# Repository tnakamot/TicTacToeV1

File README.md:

# Tic-Tac-Toe V1

This is a project to make a Tic-Tac-Toe game using Arduino Nano.

## PCB

 * The PCB has been designed with [KiCAD 6.0.10](https://www.kicad.org/).
 * The KiCAD project is available in [KiCAD/](KiCAD/) directory.

<p float="left">

</p>

The pictures below show the PCB manufactured by [OSHPARK](https://oshpark.com/).

## Software

(TODO: explain how to install the software on the Arduino Nano.)

## Parts

The list below shows the parts that this project uses.

 * Arduino Nano
   * [Product webpage at Arduino.cc](https://docs.arduino.cc/hardware/nano)
   * [Datasheet](https://docs.arduino.cc/static/2d169cbfd360faf817882e36b9f69956/A000005-datasheet.pdf)
   * This project uses a compatible clone (Arduino Nano CH340).
 * Omron B3W-9000-RG2C: button with two LEDs (red and green)
   * [Product webpage at Omron](https://components.omron.com/eu-en/products/switches/B3W-9)
   * [Datasheet](https://components.omron.com/eu-en/datasheet_pdf/A167-E1.pdf)
   * [Product page at Mouser](https://www.mouser.com/ProductDetail/Omron-Electronics/B3W-9000-RG2C?qs=QTkYtwcxD6NNQk1oSF8osQ%3D%3D): includes the link to footprint.
   * [3D Model at SnapEDA](https://www.snapeda.com/parts/B3W-9000-RG2C/Omron%20Electronics/view-part/?ref=digikey)
 * Texas Instruments 74HC165: 8-bit parallel-load shift register
   * [Product webpage at Texas Instruments](https://www.ti.com/product/SN74HC165)
   * [Datasheet](https://www.ti.com/lit/ds/symlink/sn74hc165.pdf)
 * Analog Devices MAX7219: serially interfaced, LED display driver
   * [Product webpage at Analog Devices](https://www.analog.com/en/products/max7219.html)
   * [Datasheet](https://www.analog.com/media/en/technical-documentation/data-sheets/MAX7219-MAX7221.pdf)
   * [LedControl - An Arduino library for the MAX7219 and MAX7221](http://wayoda.github.io/LedControl/index.html)
     * This program uses this library to control MAX7219.
     * The page above also explains how to wire up LEDs to MAX7219.
     
## License

TBD

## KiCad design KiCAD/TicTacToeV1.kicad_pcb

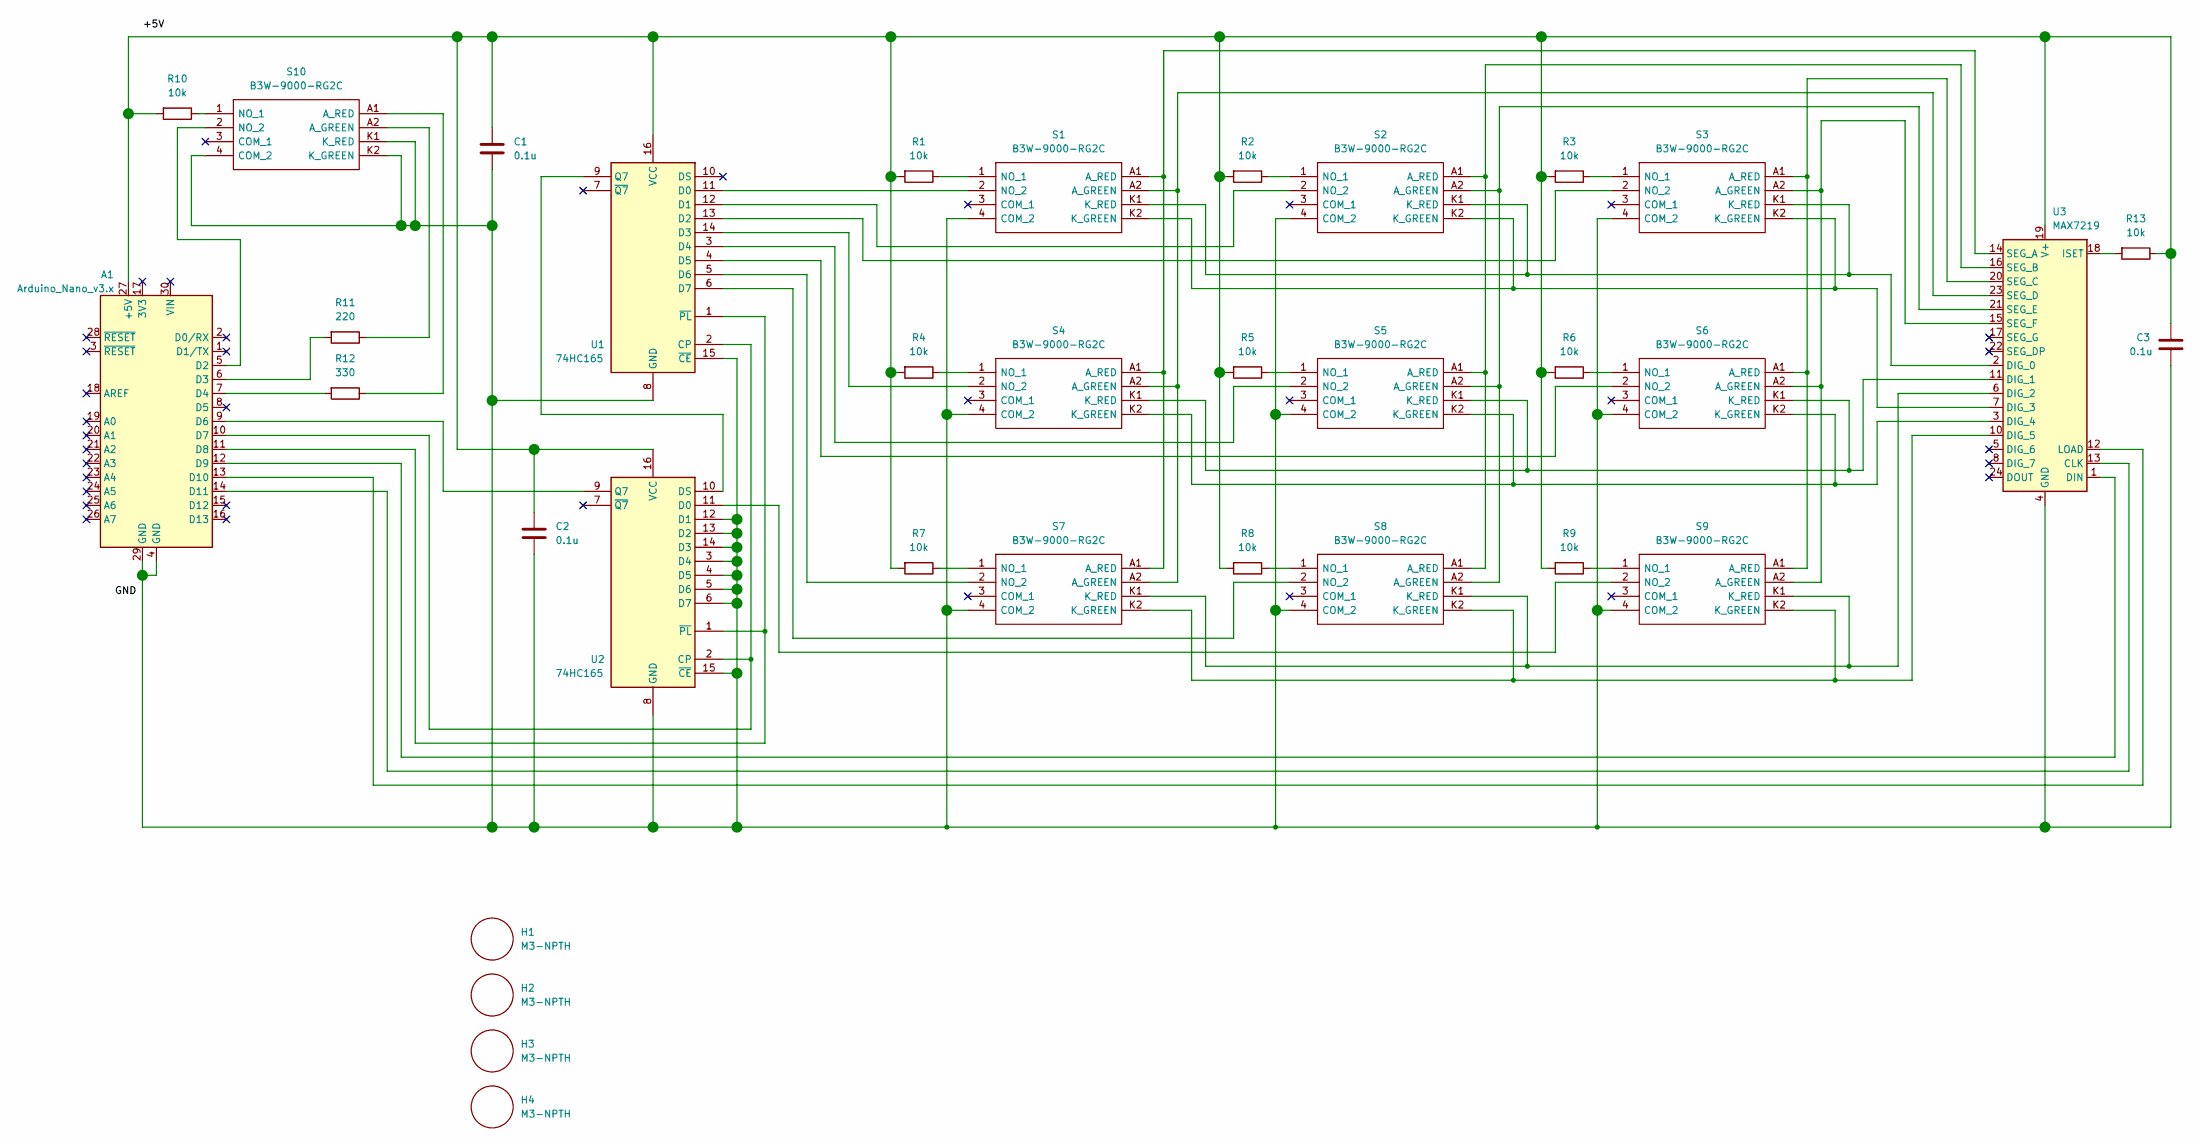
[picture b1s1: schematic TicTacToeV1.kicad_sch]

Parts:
A1: Arduino_Nano_v3.x; Arduino_Nano
C1, C2, C3: 0.1u; C_Disc_D5.0mm_W2.5mm_P5.00mm
H1, H2, H3, H4: M3-NPTH
R1, R2, R3, R4, R5, R6, R7, R8, R9, R10, R13: 10k; R_Axial_DIN0207_L6.3mm_D2.5mm_P15.24mm_Horizontal
R11: 220; R_Axial_DIN0207_L6.3mm_D2.5mm_P15.24mm_Horizontal
R12: 330; R_Axial_DIN0207_L6.3mm_D2.5mm_P15.24mm_Horizontal
S1, S2, S3, S4, S5, S6, S7, S8, S9, S10: B3W-9000-RG2C; Mouser Part Number 653-B3W-9000-RG2C
U1, U2: 74HC165; DIP-16_W7.62mm
U3: MAX7219; DIP-24_W7.62mm

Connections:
unnamed: A1.5 (D2), S10.2 (NO_2)
unnamed: A1.6 (D3), R11.2
unnamed: A1.7 (D4), R12.2
unnamed: A1.9 (D6), U2.9 (Q7)
unnamed: A1.10 (D7), U1.2 (CP), U2.2 (CP)
unnamed: A1.11 (D8), U1.1 (~PL), U2.1 (~PL)
unnamed: A1.12 (D9), U3.1 (DIN)
unnamed: A1.13 (D10), U3.12 (LOAD)
unnamed: A1.14 (D11), U3.13 (CLK)
unnamed: A1.27 (+5V), C1.1, C2.1, C3.1, R1.2, R2.2, R3.2, R4.2, R5.2, R6.2, R7.2, R8.2, R9.2, R10.2, R13.1, U1.16 (VCC), U2.16 (VCC), U3.19 (V+)
unnamed: A1.4 (GND), A1.29 (GND), C1.2, C2.2, C3.2, S1.4 (COM_2), S2.4 (COM_2), S3.4 (COM_2), S4.4 (COM_2), S5.4 (COM_2), S6.4 (COM_2), S7.4 (COM_2), S8.4 (COM_2), S9.4 (COM_2), S10.4 (COM_2), S10.K1 (K_RED), S10.K2 (K_GREEN), U1.8 (GND), U1.15 (~CE), U2.3 (D4), U2.4 (D5), U2.5 (D6), U2.6 (D7), U2.8 (GND), U2.12 (D1), U2.13 (D2), U2.14 (D3), U2.15 (~CE), U3.4 (GND), U3.9 (GND)
unnamed: R1.1, S1.1 (NO_1)
unnamed: R2.1, S2.1 (NO_1)
unnamed: R3.1, S3.1 (NO_1)
unnamed: R4.1, S4.1 (NO_1)
unnamed: R5.1, S5.1 (NO_1)
unnamed: R6.1, S6.1 (NO_1)
unnamed: R7.1, S7.1 (NO_1)
unnamed: R8.1, S8.1 (NO_1)
unnamed: R9.1, S9.1 (NO_1)
unnamed: R10.1, S10.1 (NO_1)
unnamed: R11.1, S10.A2 (A_GREEN)
unnamed: R12.1, S10.A1 (A_RED)
unnamed: R13.2, U3.18 (ISET)
unnamed: S1.2 (NO_2), U1.11 (D0)
unnamed: S1.A1 (A_RED), S4.A1 (A_RED), S7.A1 (A_RED), U3.14 (SEG_A)
unnamed: S1.A2 (A_GREEN), S4.A2 (A_GREEN), S7.A2 (A_GREEN), U3.23 (SEG_D)
unnamed: S1.K1 (K_RED), S2.K1 (K_RED), S3.K1 (K_RED), U3.2 (DIG_0)
unnamed: S1.K2 (K_GREEN), S2.K2 (K_GREEN), S3.K2 (K_GREEN), U3.7 (DIG_3)
unnamed: S2.2 (NO_2), U1.12 (D1)
unnamed: S2.A1 (A_RED), S5.A1 (A_RED), S8.A1 (A_RED), U3.16 (SEG_B)
unnamed: S2.A2 (A_GREEN), S5.A2 (A_GREEN), S8.A2 (A_GREEN), U3.21 (SEG_E)
unnamed: S3.2 (NO_2), U1.13 (D2)
unnamed: S3.A1 (A_RED), S6.A1 (A_RED), S9.A1 (A_RED), U3.20 (SEG_C)
unnamed: S3.A2 (A_GREEN), S6.A2 (A_GREEN), S9.A2 (A_GREEN), U3.15 (SEG_F)
unnamed: S4.2 (NO_2), U1.14 (D3)
unnamed: S4.K1 (K_RED), S5.K1 (K_RED), S6.K1 (K_RED), U3.11 (DIG_1)
unnamed: S4.K2 (K_GREEN), S5.K2 (K_GREEN), S6.K2 (K_GREEN), U3.3 (DIG_4)
unnamed: S5.2 (NO_2), U1.3 (D4)
unnamed: S6.2 (NO_2), U1.4 (D5)
unnamed: S7.2 (NO_2), U1.5 (D6)
unnamed: S7.K1 (K_RED), S8.K1 (K_RED), S9.K1 (K_RED), U3.6 (DIG_2)
unnamed: S7.K2 (K_GREEN), S8.K2 (K_GREEN), S9.K2 (K_GREEN), U3.10 (DIG_5)
unnamed: S8.2 (NO_2), U1.6 (D7)
unnamed: S9.2 (NO_2), U2.11 (D0)
unnamed: U1.9 (Q7), U2.10 (DS)

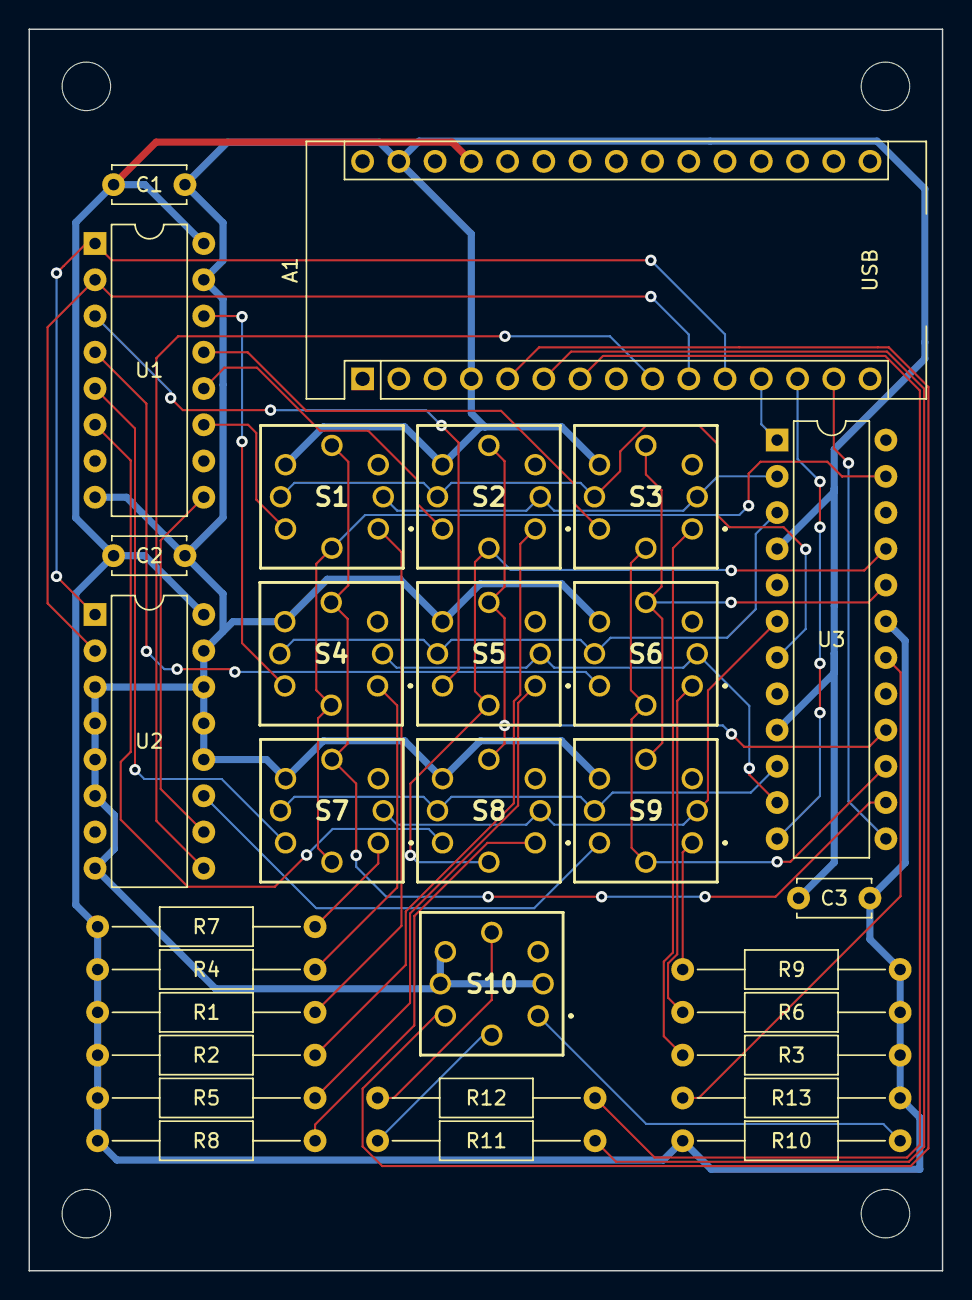
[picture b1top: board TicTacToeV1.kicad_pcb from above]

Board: 2 copper layers, 64.0 x 87.0 mm, 34 parts (0 on the bottom side), 46 nets.

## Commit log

2023-01-09 Updated for production by OSHPARK
2023-01-17 Ignore backup and cache.
2023-01-17 Moved the KiCAD project to a sub-directory.
2023-01-22 Updated the register value based on the prototyping on the breadboard.
2023-01-22 An arduino test code to check the behavior of the reset button and main 9 buttons.
2023-01-22 Makefile for WSL2 environment.
2023-01-22 Now 'upload' is the default goal.
2023-01-22 Run serial monitor after upload.
2023-01-22 Print the main button states.
2023-01-22 Imported LedControl class from http://wayoda.github.io/LedControl/index.html
2023-01-22 Code to test the LedControl class.
2023-01-22 Made some document.
2023-01-22 Complete IO test.
2023-01-22 CRLF -> LF
2023-01-22 Added PCB images from KiCAD.
2023-01-22 Change the size of images
2023-01-22 Show images side-by-side
2023-01-22 Added pitcures of a manufactured PCB.
2023-01-22 Adjusted the size of pictured.
2023-01-22 Shrinked the pictures more.
2023-01-22 Added some more info to the documentation.
2023-01-22 Download arduino-cli.exe when it is missing.
2023-01-22 Started to write the main program.
2023-01-22 Improved the inline document.
2023-01-23 Detect the button state change.
2023-01-23 Detect the button release events only.
2023-01-23 Turn on LEDs when the button is pressed.
2023-01-23 New function to evaluate the territory.
2023-01-23 Added the picture of the PCB with parts mounted.
2023-01-23 Fixed the file name typo.
2023-01-23 Implemented draw().
2023-01-23 Enable the reset button during the play.
2023-01-23 Flash the reset button when the red or green player wins.
2023-01-23 Finished the implementation.
2023-01-23 Adjust the image size.
2023-01-27 Added case design.
